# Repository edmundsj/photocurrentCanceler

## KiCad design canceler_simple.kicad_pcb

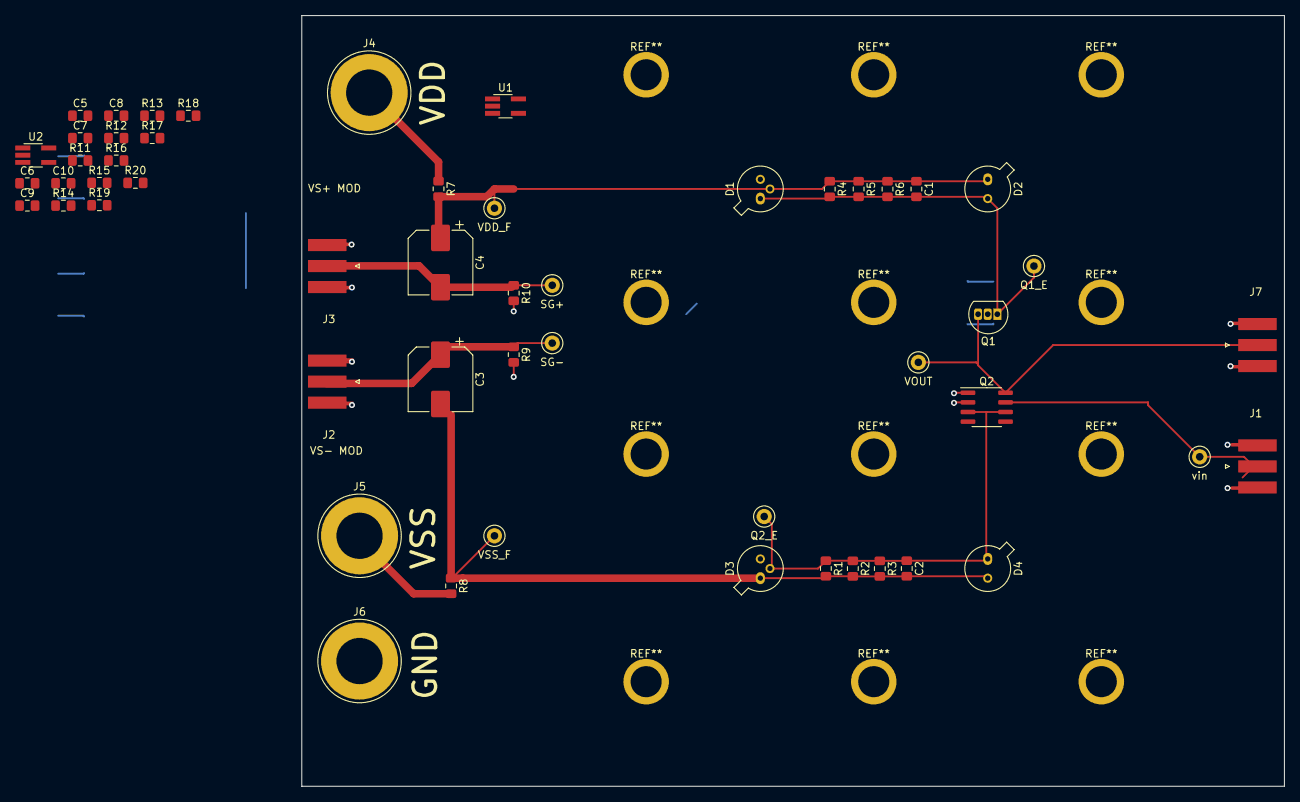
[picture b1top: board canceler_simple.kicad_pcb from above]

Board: 2 copper layers, 129.5 x 101.6 mm, 53 parts (0 on the bottom side), 21 nets.

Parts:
C1, C2: 10p; C_0805_2012Metric_Pad1.15x1.40mm_HandSolder
C3, C4: CP1; CP_Elec_8x10
C5, C6, C9, C10: 2.2u; C_0805_2012Metric_Pad1.15x1.40mm_HandSolder
C7, C8: 1u; C_0805_2012Metric_Pad1.15x1.40mm_HandSolder
D1, D3: Photodiode_can; TO-46-3
D2, D4: D_Photo; TO-46-2
J1, J2, J3, J7: Conn_Coaxial; CON-SMA-EDGE-S
J4, J5, J6: Conn_01x01_Female; Banana_Jack_1Pin
Q1: Q_PNP_Darlington_EBC; TO-92L_Inline
Q2: SSM2212; SOIC-8_3.9x4.9mm_P1.27mm
R1: 10M; R_0805_2012Metric_Pad1.15x1.40mm_HandSolder
R2: 1M; R_0805_2012Metric_Pad1.15x1.40mm_HandSolder
R3, R16, R17: 100k; R_0805_2012Metric_Pad1.15x1.40mm_HandSolder
R4: 15M; R_0805_2012Metric_Pad1.15x1.40mm_HandSolder
R5: 1.5M; R_0805_2012Metric_Pad1.15x1.40mm_HandSolder
R6: 150k; R_0805_2012Metric_Pad1.15x1.40mm_HandSolder
R7, R8: 1k; R_0805_2012Metric_Pad1.15x1.40mm_HandSolder
R9, R10: 0; R_0805_2012Metric_Pad1.15x1.40mm_HandSolder
R11, R12, R13, R14: 0R; R_0805_2012Metric_Pad1.15x1.40mm_HandSolder
R15, R18: 8.7k; R_0805_2012Metric_Pad1.15x1.40mm_HandSolder
R19, R20: 470; R_0805_2012Metric_Pad1.15x1.40mm_HandSolder
TP1: SG-; TestPoint_Keystone_5000-5004_Miniature
TP2: SG+; TestPoint_Keystone_5000-5004_Miniature
TP3: Q2_E; TestPoint_Keystone_5000-5004_Miniature
TP4: VSS_F; TestPoint_Keystone_5000-5004_Miniature
TP5: Q1_E; TestPoint_Keystone_5000-5004_Miniature
TP6: VOUT; TestPoint_Keystone_5000-5004_Miniature
TP7: VDD_F; TestPoint_Keystone_5000-5004_Miniature
TP8: vin; TestPoint_Keystone_5000-5004_Miniature
U1: ADP7118ARDZ; TSOT-23-5_HandSoldering
U2: ADP7182AUJZ; TSOT-23-5_HandSoldering

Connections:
/Q1_E: C1.2, D1.1, D2.2, Q1.1, R4.2, R5.2, R6.2, TP5.1
/Q2_E: C2.1, D3.2, D4.1, Q2.3, Q2.6, R1.1, R2.1, R3.1, TP3.1
/SG_NEG: C3.1, J2.1, R9.1, TP1.1
/SG_POS: C4.2, J3.1, R10.1, TP2.1
/VDD_Filtered: C1.1, C4.1, D1.2, D2.1, R4.1, R5.1, R6.1, R7.2, TP7.1
/VIN: J1.1, Q2.7, TP8.1
/VOUT: J7.1, Q1.3, Q2.8, TP6.1
/VSS_Filtered: C2.2, C3.2, D3.1, D4.2, R1.2, R2.2, R3.2, R8.1, TP4.1
/power/VDD: C9.1, R14.1, R17.1, R19.2, U1.5
/power/VEX+: C5.1, R11.2, R14.2
/power/VEX-: C6.2, R12.2, R13.2
/power/VSS: C10.2, R13.1, R16.2, R20.1, U2.5
GND: C5.2, C6.1, C9.2, C10.1, D1.3, D3.3, J1.2, J2.2, J3.2, J6.1, J7.2, Q1.2, Q2.1, Q2.2, R9.2, R10.2, R15.1, R18.2, U1.2, U2.1
unnamed: C7.1, R17.2, R18.1, U1.4
unnamed: C7.2, R19.1
unnamed: C8.1, R15.2, R16.1, U2.4
unnamed: C8.2, R20.2
unnamed: R11.1, U1.1, U1.3
unnamed: R12.1, U2.2, U2.3
VDD: J4.1, R7.1
VSS: J5.1, R8.2

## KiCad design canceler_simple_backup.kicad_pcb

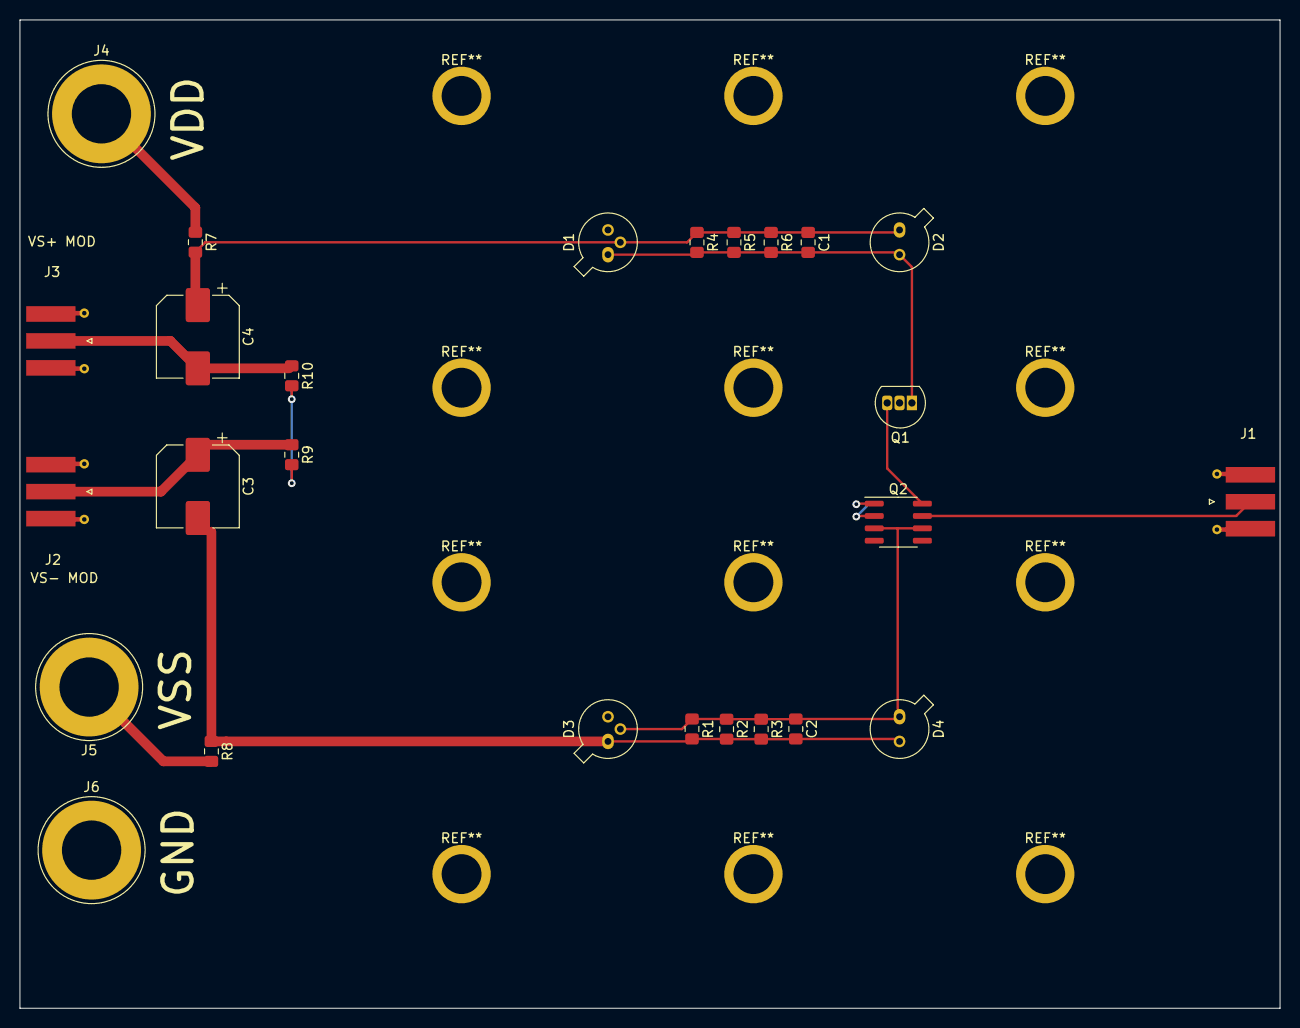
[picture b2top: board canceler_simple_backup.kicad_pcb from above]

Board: 2 copper layers, 129.5 x 101.6 mm, 26 parts (0 on the bottom side), 11 nets.

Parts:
C1, C2: 10p; C_0805_2012Metric_Pad1.15x1.40mm_HandSolder
C3, C4: CP1; CP_Elec_8x10
D1, D3: Photodiode_can; TO-46-3
D2, D4: D_Photo; TO-46-2
J1, J2, J3: Conn_Coaxial; CON-SMA-EDGE-S
J4, J5, J6: Conn_01x01_Female; Banana_Jack_1Pin
Q1: Q_PNP_Darlington_EBC; TO-92L_Inline
Q2: SSM2212; SOIC-8_3.9x4.9mm_P1.27mm
R1: 10M; R_0805_2012Metric_Pad1.15x1.40mm_HandSolder
R2: 1M; R_0805_2012Metric_Pad1.15x1.40mm_HandSolder
R3: 100k; R_0805_2012Metric_Pad1.15x1.40mm_HandSolder
R4: 15M; R_0805_2012Metric_Pad1.15x1.40mm_HandSolder
R5: 1.5M; R_0805_2012Metric_Pad1.15x1.40mm_HandSolder
R6: 150k; R_0805_2012Metric_Pad1.15x1.40mm_HandSolder
R7, R8: 1k; R_0805_2012Metric_Pad1.15x1.40mm_HandSolder
R9, R10: 0; R_0805_2012Metric_Pad1.15x1.40mm_HandSolder

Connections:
GND: D1.3, D3.3, J1.2, J2.2, J3.2, J6.1, Q1.2, Q2.1, Q2.2, R9.2, R10.2
unnamed: C1.1, C4.1, D1.2, D2.1, R4.1, R5.1, R6.1, R7.2
unnamed: C1.2, D1.1, D2.2, Q1.1, R4.2, R5.2, R6.2
unnamed: C2.1, D3.2, D4.1, Q2.3, Q2.6, R1.1, R2.1, R3.1
unnamed: C2.2, C3.2, D3.1, D4.2, R1.2, R2.2, R3.2, R8.1
unnamed: C3.1, J2.1, R9.1
unnamed: C4.2, J3.1, R10.1
unnamed: J1.1, Q2.7
unnamed: Q1.3, Q2.8
VDD: J4.1, R7.1
VSS: J5.1, R8.2
